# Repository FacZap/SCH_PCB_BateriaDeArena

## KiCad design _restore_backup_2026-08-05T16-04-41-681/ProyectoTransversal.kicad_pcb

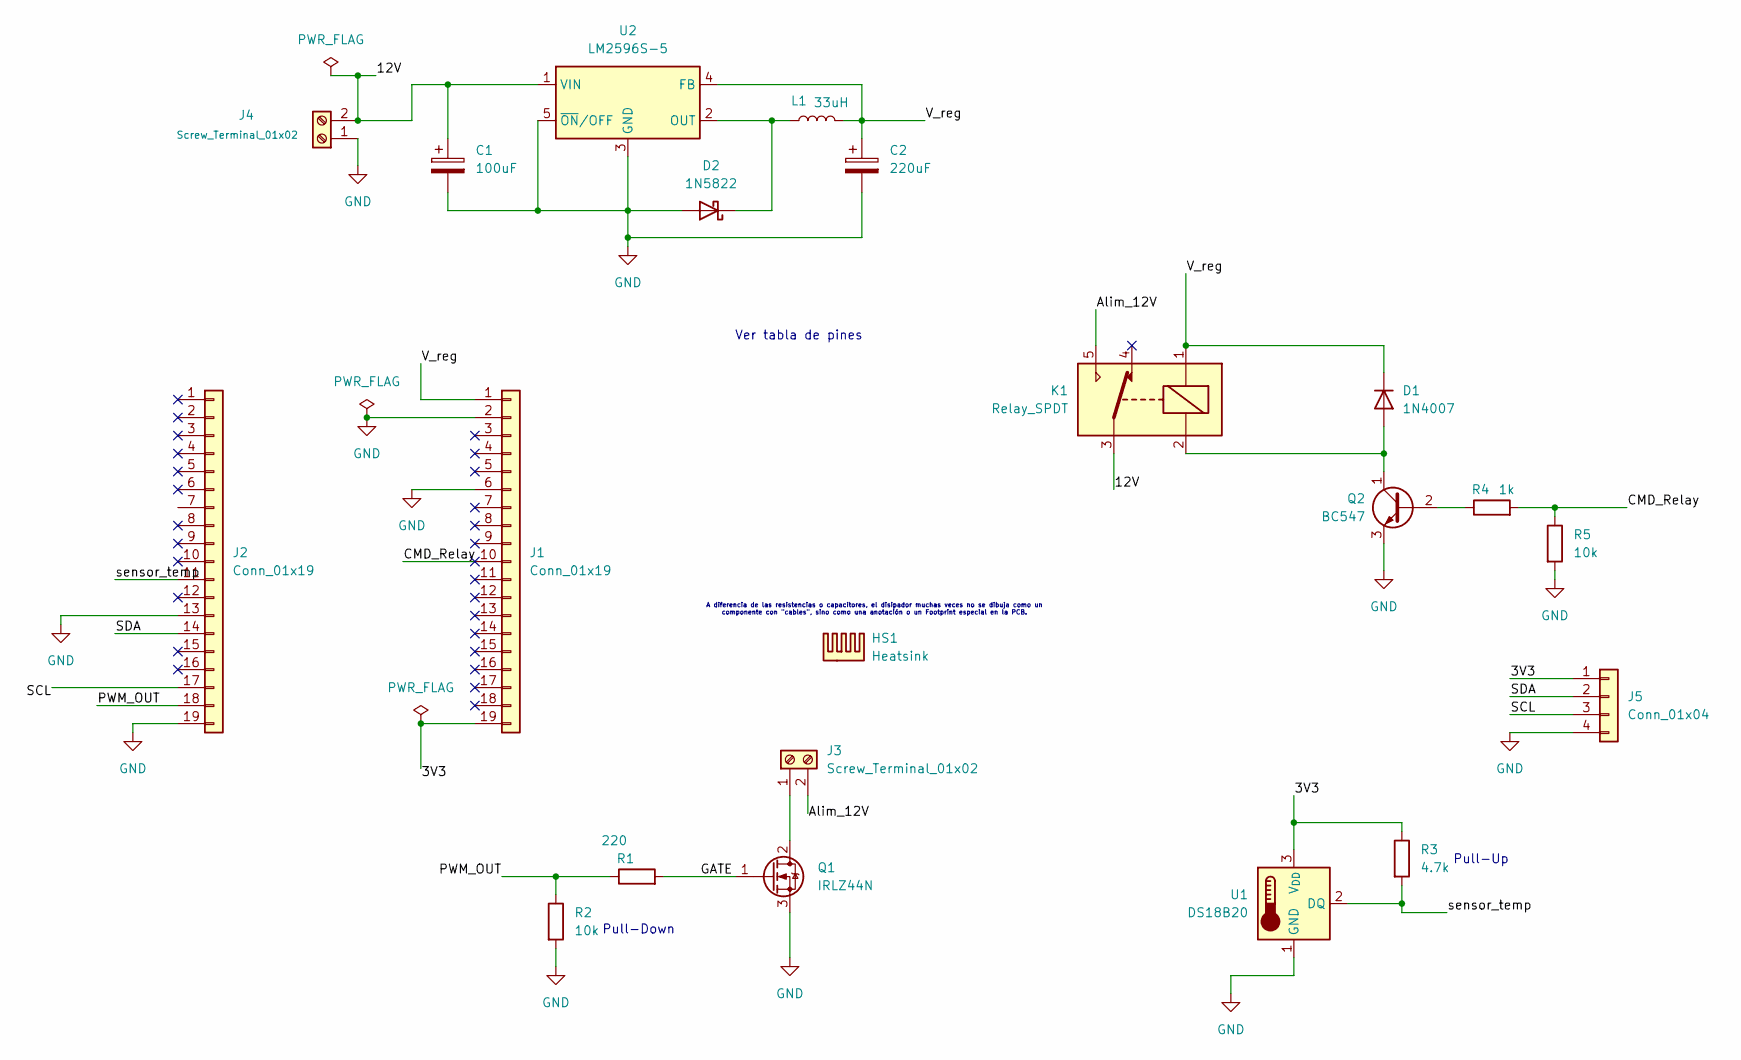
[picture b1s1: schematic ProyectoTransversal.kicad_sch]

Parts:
C1: 100uF; CP_Elec_6.3x7.7
C2: 220uF; CP_Elec_8x10.5
D1: 1N4007; D_DO-41_SOD81_P10.16mm_Horizontal
D2: 1N5822; D_DO-201AD_P15.24mm_Horizontal
HS1: Heatsink; Heatsink_Fischer_SK104-STC-STIC_35x13mm_2xDrill2.5mm
J1, J2: Conn_01x19; PinHeader_1x19_P2.54mm_Vertical
J3, J4: Screw_Terminal_01x02; TerminalBlock_MaiXu_MX126-5.0-02P_1x02_P5.00mm
J5: Conn_01x04; PinHeader_1x04_P2.54mm_Vertical
K1: Relay_SPDT; Relay_SPDT_SANYOU_SRD_Series_Form_C
L1: 33uH; L_Radial_D10.5mm_P5.00mm_Abacron_AISR-01
Q1: IRLZ44N; TO-220-3_Vertical
Q2: BC547; TO-92_Inline
R1: 220; R_1206_3216Metric
R2, R5: 10k; R_1206_3216Metric
R3: 4.7k; R_1206_3216Metric
R4: 1k; R_1206_3216Metric
U1: DS18B20; TO-92_Inline
U2: LM2596S-5; TO-220-5_Vertical

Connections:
/3V3: J1.19, J5.1, R3.1, U1.3 (V_{DD})
/12V: C1.1, J4.2, K1.3, U2.1 (VIN)
/Alim_12V: J3.2, K1.5
/CMD_Relay: J1.10, R4.2, R5.1
/GATE: Q1.1 (G), R1.2
/PWM_OUT: J2.18, R1.1, R2.1
/SCL: J2.17, J5.3
/SDA: J2.14, J5.2
/V_reg: C2.1, D1.1 (K), J1.1, K1.1, L1.2, U2.4 (FB)
/sensor_temp: J2.11, R3.2, U1.2 (DQ)
GND: C1.2, C2.2, D2.2 (A), J1.2, J1.6, J2.13, J2.19, J4.1, J5.4, Q1.3 (S), Q2.3 (E), R2.2, R5.2, U1.1 (GND), U2.3 (GND), U2.5 (~ON/OFF)
unnamed: D1.2 (A), K1.2, Q2.1 (C)
unnamed: D2.1 (K), L1.1, U2.2 (OUT)
unnamed: J3.1, Q1.2 (D)
unnamed: Q2.2 (B), R4.1

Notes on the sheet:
A diferencia de las resistencias o capacitores, el disipador muchas veces no se dibuja como un componente con "cables", sino como una anotación o un Footprint especial en la PCB.
Pull-Up
Pull-Down
Ver tabla de pines

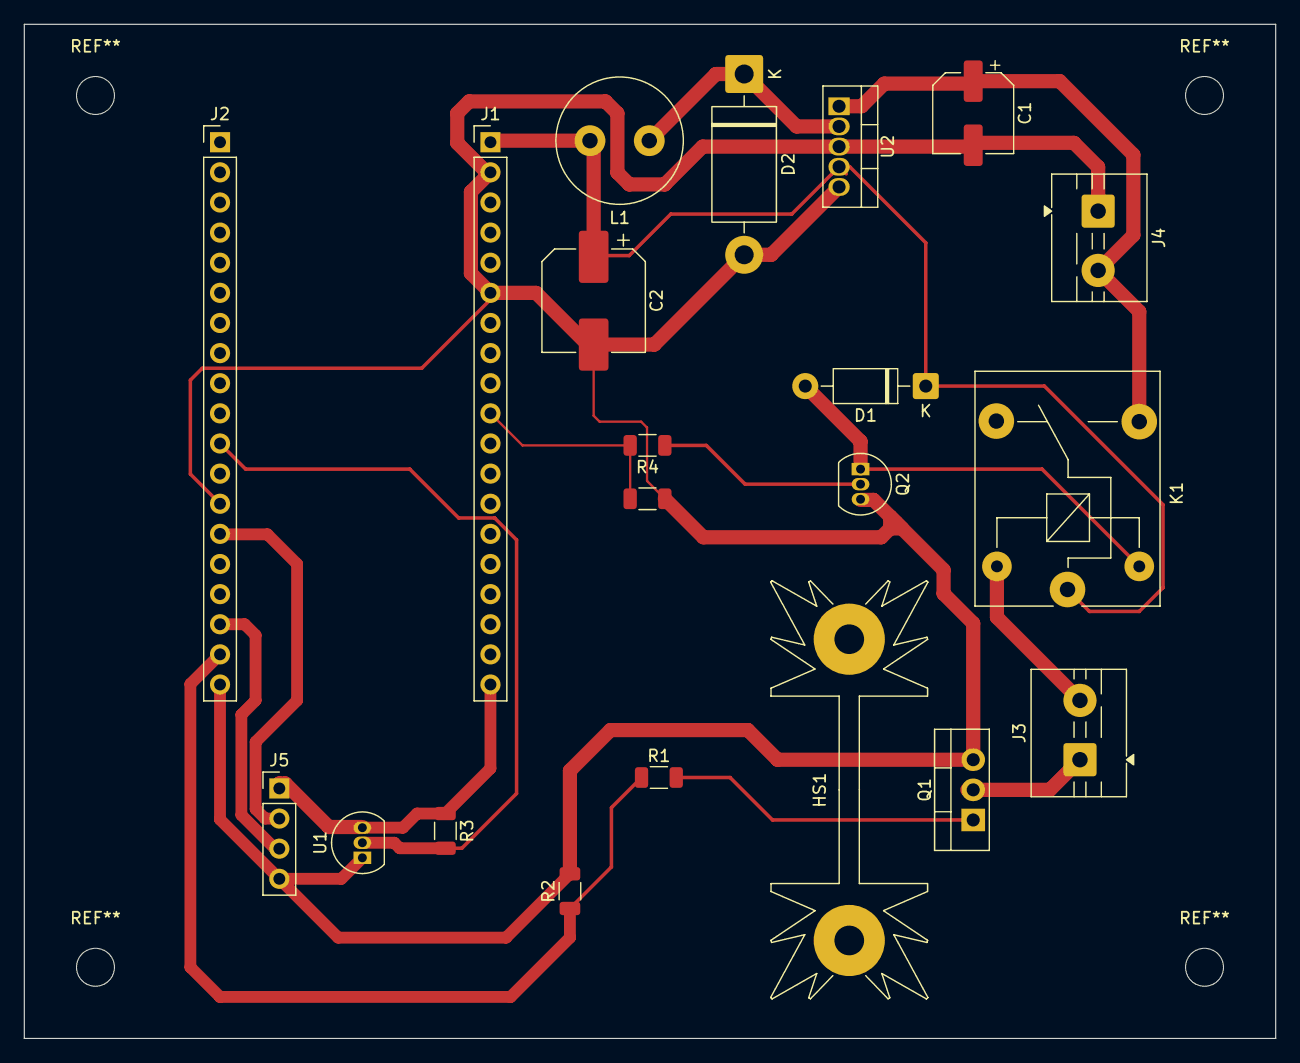
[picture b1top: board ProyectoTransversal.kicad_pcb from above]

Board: 2 copper layers, 105.5 x 85.5 mm, 21 parts (0 on the bottom side), 15 nets.

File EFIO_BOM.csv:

"Reference","Qty","Value","Footprint","Datasheet","Tecnologia"
"C1","1","100uF","Capacitor_SMD:CP_Elec_6.3x7.7","","SMD"
"C2","1","220uF","Capacitor_SMD:CP_Elec_8x10.5","","SMD"
"R1","1","220","Resistor_SMD:R_1206_3216Metric","","SMD"
"R2,R5","2","10k","Resistor_SMD:R_1206_3216Metric","","SMD"
"R3","1","4.7k","Resistor_SMD:R_1206_3216Metric","","SMD"
"R4","1","1k","Resistor_SMD:R_1206_3216Metric","","SMD"
"D1","1","1N4007","Diode_THT:D_DO-41_SOD81_P10.16mm_Horizontal","http://www.vishay.com/docs/88503/1n4001.pdf","THT"
"D2","1","1N5822","Diode_THT:D_DO-201AD_P15.24mm_Horizontal","http://www.vishay.com/docs/88526/1n5820.pdf","THT"
"HS1","1","Heatsink","Heatsink:Heatsink_Fischer_SK104-STC-STIC_35x13mm_2xDrill2.5mm","","THT"
"J1,J2","2","Conn_01x19","Connector_PinHeader_2.54mm:PinHeader_1x19_P2.54mm_Vertical","","THT"
"J3,J4","2","Screw_Terminal_01x02","TerminalBlock:TerminalBlock_MaiXu_MX126-5.0-02P_1x02_P5.00mm","","THT"
"J5","1","Conn_01x04","Connector_PinHeader_2.54mm:PinHeader_1x04_P2.54mm_Vertical","","THT"
"K1","1","Relay_SPDT","Relay_THT:Relay_SPDT_SANYOU_SRD_Series_Form_C","","THT"
"L1","1","33uH","Inductor_THT:L_Radial_D10.5mm_P5.00mm_Abacron_AISR-01","","THT"
"Q1","1","IRLZ44N","Package_TO_SOT_THT:TO-220-3_Vertical","http://www.irf.com/product-info/datasheets/data/irlz44n.pdf","THT"
"Q2","1","BC547","Package_TO_SOT_THT:TO-92_Inline","https://www.onsemi.com/pub/Collateral/BC550-D.pdf","THT"
"U1","1","DS18B20","Package_TO_SOT_THT:TO-92_Inline","http://datasheets.maximintegrated.com/en/ds/DS18B20.pdf","THT"
"U2","1","LM2596S-5","Package_TO_SOT_THT:TO-220-5_Vertical","http://www.ti.com/lit/ds/symlink/lm2596.pdf","THT"

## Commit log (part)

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2026-06-26 Add more components
2026-06-29 Continue
2026-06-29 Add voltage regulator
2026-06-29 work day 29/06/26
2026-06-30 Finish PCB connections and ERC
